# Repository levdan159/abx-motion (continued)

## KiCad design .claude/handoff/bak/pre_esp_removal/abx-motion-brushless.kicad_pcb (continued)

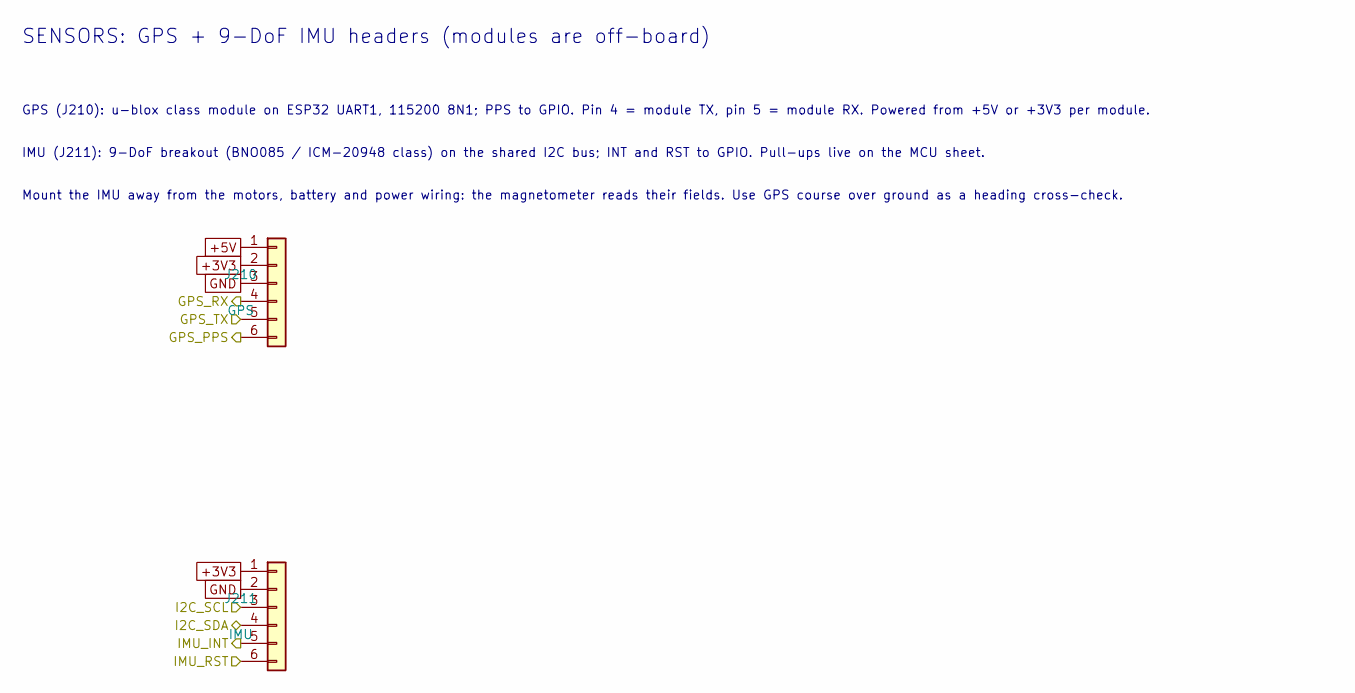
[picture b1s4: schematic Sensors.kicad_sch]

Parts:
J210: GPS; JST_PH_B6B-PH-K_1x06_P2.00mm_Vertical
J211: IMU; JST_PH_B6B-PH-K_1x06_P2.00mm_Vertical

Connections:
+3V3: J210.2, J211.1; also elsewhere on the board
+5V: J210.1; also elsewhere on the board
/GPS_PPS: J210.6; also elsewhere on the board
/GPS_RX: J210.4; also elsewhere on the board
/GPS_TX: J210.5; also elsewhere on the board
/I2C_SCL: J211.3; also elsewhere on the board
/I2C_SDA: J211.4; also elsewhere on the board
/IMU_INT: J211.5; also elsewhere on the board
/IMU_RST: J211.6; also elsewhere on the board

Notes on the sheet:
SENSORS: GPS + 9-DoF IMU headers (modules are off-board)
GPS (J210): u-blox class module on ESP32 UART1, 115200 8N1; PPS to GPIO. Pin 4 = module TX, pin 5 = module RX. Powered from +5V or +3V3 per module.
IMU (J211): 9-DoF breakout (BNO085 / ICM-20948 class) on the shared I2C bus; INT and RST to GPIO. Pull-ups live on the MCU sheet.
Mount the IMU away from the motors, battery and power wiring: the magnetometer reads their fields. Use GPS course over ground as a heading cross-check.

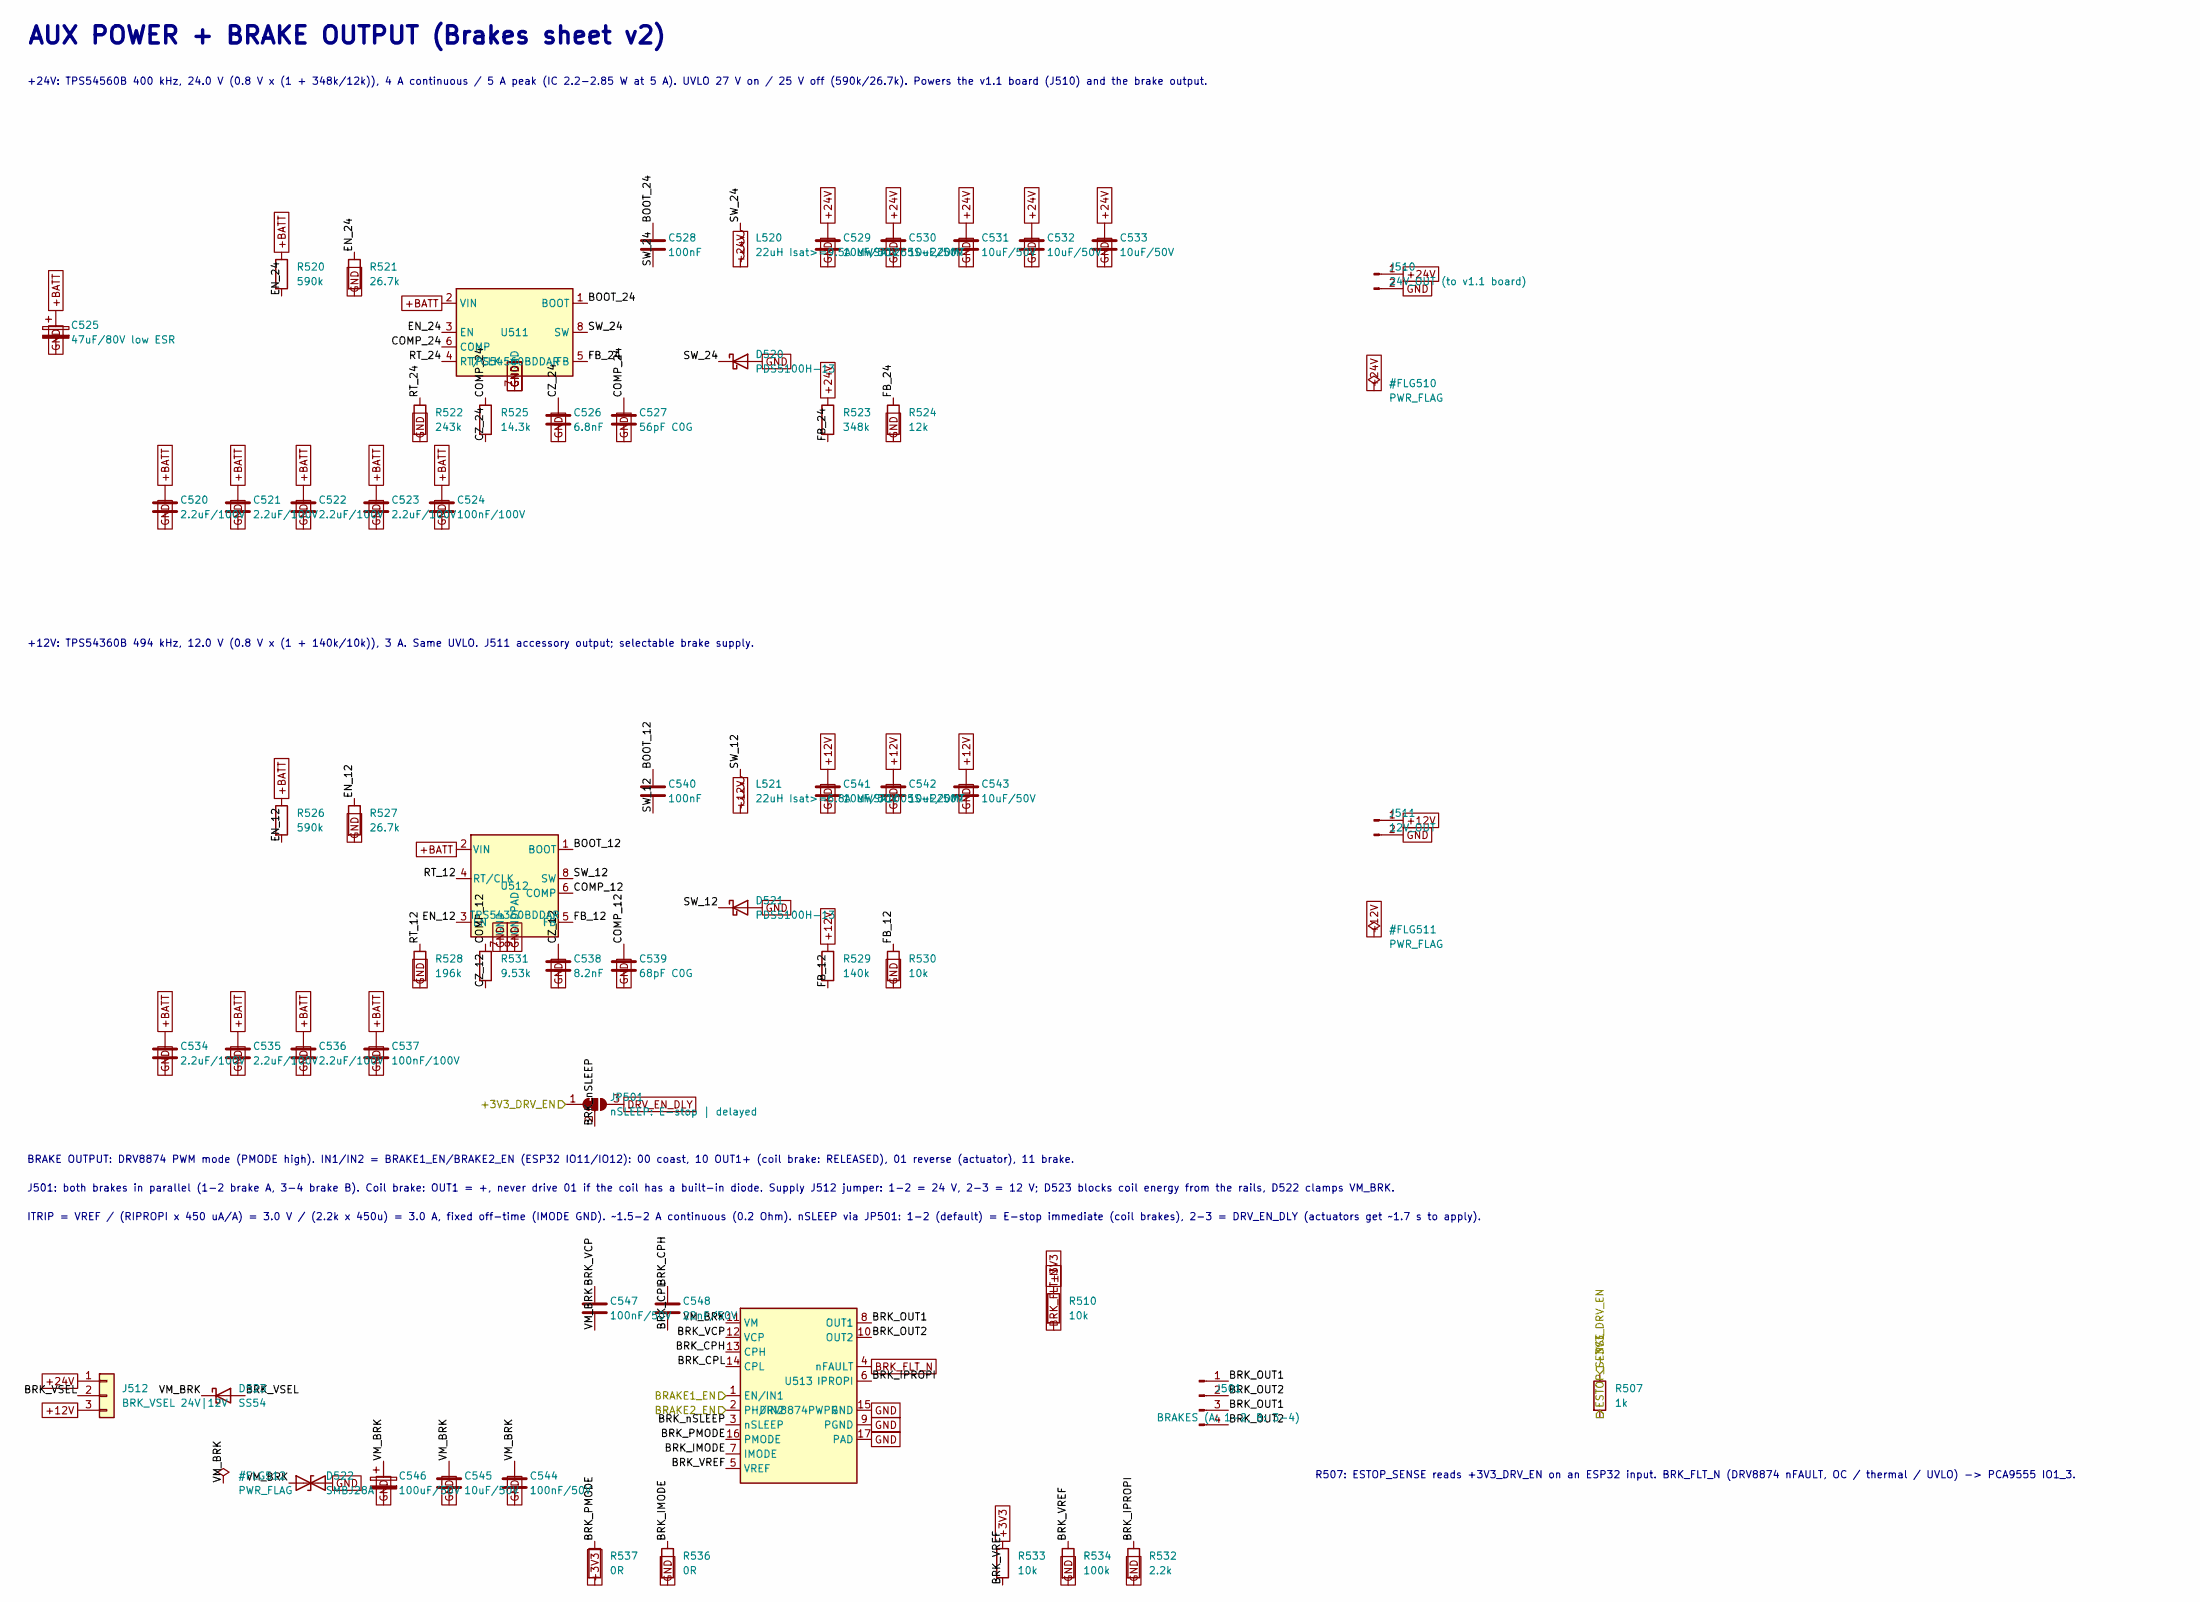
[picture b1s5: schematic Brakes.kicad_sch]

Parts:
C520, C521, C522, C523, C534, C535, C536: 2.2uF/100V; C_1210_3225Metric
C524, C537: 100nF/100V; C_0603_1608Metric
C525: 47uF/80V low ESR; CP_Elec_10x10.5
C526: 6.8nF; C_0603_1608Metric
C527: 56pF C0G; C_0603_1608Metric
C528, C540: 100nF; C_0603_1608Metric
C529, C530, C531, C532, C533, C541, C542, C543, C545: 10uF/50V; C_1210_3225Metric
C538: 8.2nF; C_0603_1608Metric
C539: 68pF C0G; C_0603_1608Metric
C544, C547: 100nF/50V; C_0603_1608Metric
C546: 100uF/50V; CP_Elec_8x10.5
C548: 22nF/50V; C_0603_1608Metric
D520, D521: PDS5100H-13; D_PowerDI-5
D522: SMBJ28A; D_SMB
D523: SS54; D_SMC
J501: BRAKES (A: 1-2, B: 3-4); TerminalBlock_Phoenix_MKDS-1,5-4-5.08_1x04_P5.08mm_Horizont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
J510: 24V_OUT (to v1.1 board); TerminalBlock_Phoenix_MKDS-1,5-2-5.08_1x02_P5.08mm_Horizont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
J511: 12V_OUT; TerminalBlock_Phoenix_MKDS-1,5-2-5.08_1x02_P5.08mm_Horizont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
J512: BRK_VSEL 24V|12V; PinHeader_1x03_P2.54mm_Vertical
JP501: nSLEEP: E-stop | delayed; SolderJumper-3_P1.3mm_Bridged12_RoundedPad1.0x1.5mm
L520: 22uH Isat>=9.5A MWSA1265S-220MT; L_Sunlord_MWSA1265S
L521: 22uH Isat>=6.8A MWSA1005S-220MT; L_Sunlord_MWSA1005S
R507: 1k; R_0603_1608Metric
R510, R530, R533: 10k; R_0603_1608Metric
R520, R526: 590k; R_0805_2012Metric
R521, R527: 26.7k; R_0603_1608Metric
R522: 243k; R_0603_1608Metric
R523: 348k; R_0603_1608Metric
R524: 12k; R_0603_1608Metric
R525: 14.3k; R_0603_1608Metric
R528: 196k; R_0603_1608Metric
R529: 140k; R_0603_1608Metric
R531: 9.53k; R_0603_1608Metric
R532: 2.2k; R_0603_1608Metric
R534: 100k; R_0603_1608Metric
R536, R537: 0R; R_0603_1608Metric
U511: TPS54560BDDAR; TI_SO-PowerPAD-8_ThermalVias
U512: TPS54360BDDAR; TI_SO-PowerPAD-8_ThermalVias
U513: DRV8874PWPR; HTSSOP-16-1EP_4.4x5mm_P0.65mm_EP3.4x5mm_Mask3x3mm_ThermalVi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

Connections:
+3V3: R510.1, R533.1, R537.2; also elsewhere on the board
+12V: C541.1, C542.1, C543.1, J511.1, J512.3, L521.2, R529.1
+24V: C529.1, C530.1, C531.1, C532.1, C533.1, J510.1, J512.1, L520.2, R523.1
+BATT: C520.1, C521.1, C522.1, C523.1, C524.1, C525.1, C534.1, C535.1, C536.1, C537.1, R520.1, R526.1, U511.2 (VIN), U512.2 (VIN); also elsewhere on the board
/+3V3_DRV_EN: JP501.1 (A), R507.1; also elsewhere on the board
/BRAKE1_EN: U513.1 (EN/IN1); also elsewhere on the board
/BRAKE2_EN: U513.2 (PH/IN2); also elsewhere on the board
/Brakes/BOOT_12: C540.1, U512.1 (BOOT)
/Brakes/BOOT_24: C528.1, U511.1 (BOOT)
/Brakes/BRK_CPH: C548.1, U513.13 (CPH)
/Brakes/BRK_CPL: C548.2, U513.14 (CPL)
/Brakes/BRK_IMODE: R536.1, U513.7 (IMODE)
/Brakes/BRK_IPROPI: R532.1, U513.6 (IPROPI)
/Brakes/BRK_OUT1: J501.1, J501.3, U513.8 (OUT1)
/Brakes/BRK_OUT2: J501.2, J501.4, U513.10 (OUT2)
/Brakes/BRK_PMODE: R537.1, U513.16 (PMODE)
/Brakes/BRK_VCP: C547.1, U513.12 (VCP)
/Brakes/BRK_VREF: R533.2, R534.1, U513.5 (VREF)
/Brakes/BRK_VSEL: D523.2 (A), J512.2
/Brakes/BRK_nSLEEP: JP501.2 (C), U513.3 (nSLEEP)
/Brakes/COMP_12: C539.1, R531.1, U512.6 (COMP)
/Brakes/COMP_24: C527.1, R525.1, U511.6 (COMP)
/Brakes/CZ_12: C538.1, R531.2
/Brakes/CZ_24: C526.1, R525.2
/Brakes/EN_12: R526.2, R527.1, U512.3 (EN)
/Brakes/EN_24: R520.2, R521.1, U511.3 (EN)
/Brakes/FB_12: R529.2, R530.1, U512.5 (FB)
/Brakes/FB_24: R523.2, R524.1, U511.5 (FB)
/Brakes/RT_12: R528.1, U512.4 (RT/CLK)
/Brakes/RT_24: R522.1, U511.4 (RT/CLK)
/Brakes/SW_12: C540.2, D521.1 (K), L521.1, U512.8 (SW)
/Brakes/SW_24: C528.2, D520.1 (K), L520.1, U511.8 (SW)
/Brakes/VM_BRK: C544.1, C545.1, C546.1, C547.2, D522.1 (A1), D523.1 (K), U513.11 (VM)
/ESTOP_SENSE: R507.2; also elsewhere on the board
BRK_FLT_N: R510.2, U513.4 (nFAULT); also elsewhere on the board
DRV_EN_DLY: JP501.3 (B); also elsewhere on the board

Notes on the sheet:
AUX POWER + BRAKE OUTPUT (Brakes sheet v2)
+24V: TPS54560B 400 kHz, 24.0 V (0.8 V x (1 + 348k/12k)), 4 A continuous / 5 A peak (IC 2.2-2.85 W at 5 A). UVLO 27 V on / 25 V off (590k/26.7k). Powers the v1.1 board (J510) and the brake output.
+12V: TPS54360B 494 kHz, 12.0 V (0.8 V x (1 + 140k/10k)), 3 A. Same UVLO. J511 accessory output; selectable brake supply.
BRAKE OUTPUT: DRV8874 PWM mode (PMODE high). IN1/IN2 = BRAKE1_EN/BRAKE2_EN (ESP32 IO11/IO12): 00 coast, 10 OUT1+ (coil brake: RELEASED), 01 reverse (actuator), 11 brake.
J501: both brakes in parallel (1-2 brake A, 3-4 brake B). Coil brake: OUT1 = +, never drive 01 if the coil has a built-in diode. Supply J512 jumper: 1-2 = 24 V, 2-3 = 12 V; D523 blocks coil energy from the rails, D522 clamps VM_BRK.
ITRIP = VREF / (RIPROPI x 450 uA/A) = 3.0 V / (2.2k x 450u) = 3.0 A, fixed off-time (IMODE GND). ~1.5-2 A continuous (0.2 Ohm). nSLEEP via JP501: 1-2 (default) = E-stop immediate (coil brakes), 2-3 = DRV_EN_DLY (actuators get ~1.7 s to apply).
R507: ESTOP_SENSE reads +3V3_DRV_EN on an ESP32 input. BRK_FLT_N (DRV8874 nFAULT, OC / thermal / UVLO) -> PCA9555 IO1_3.

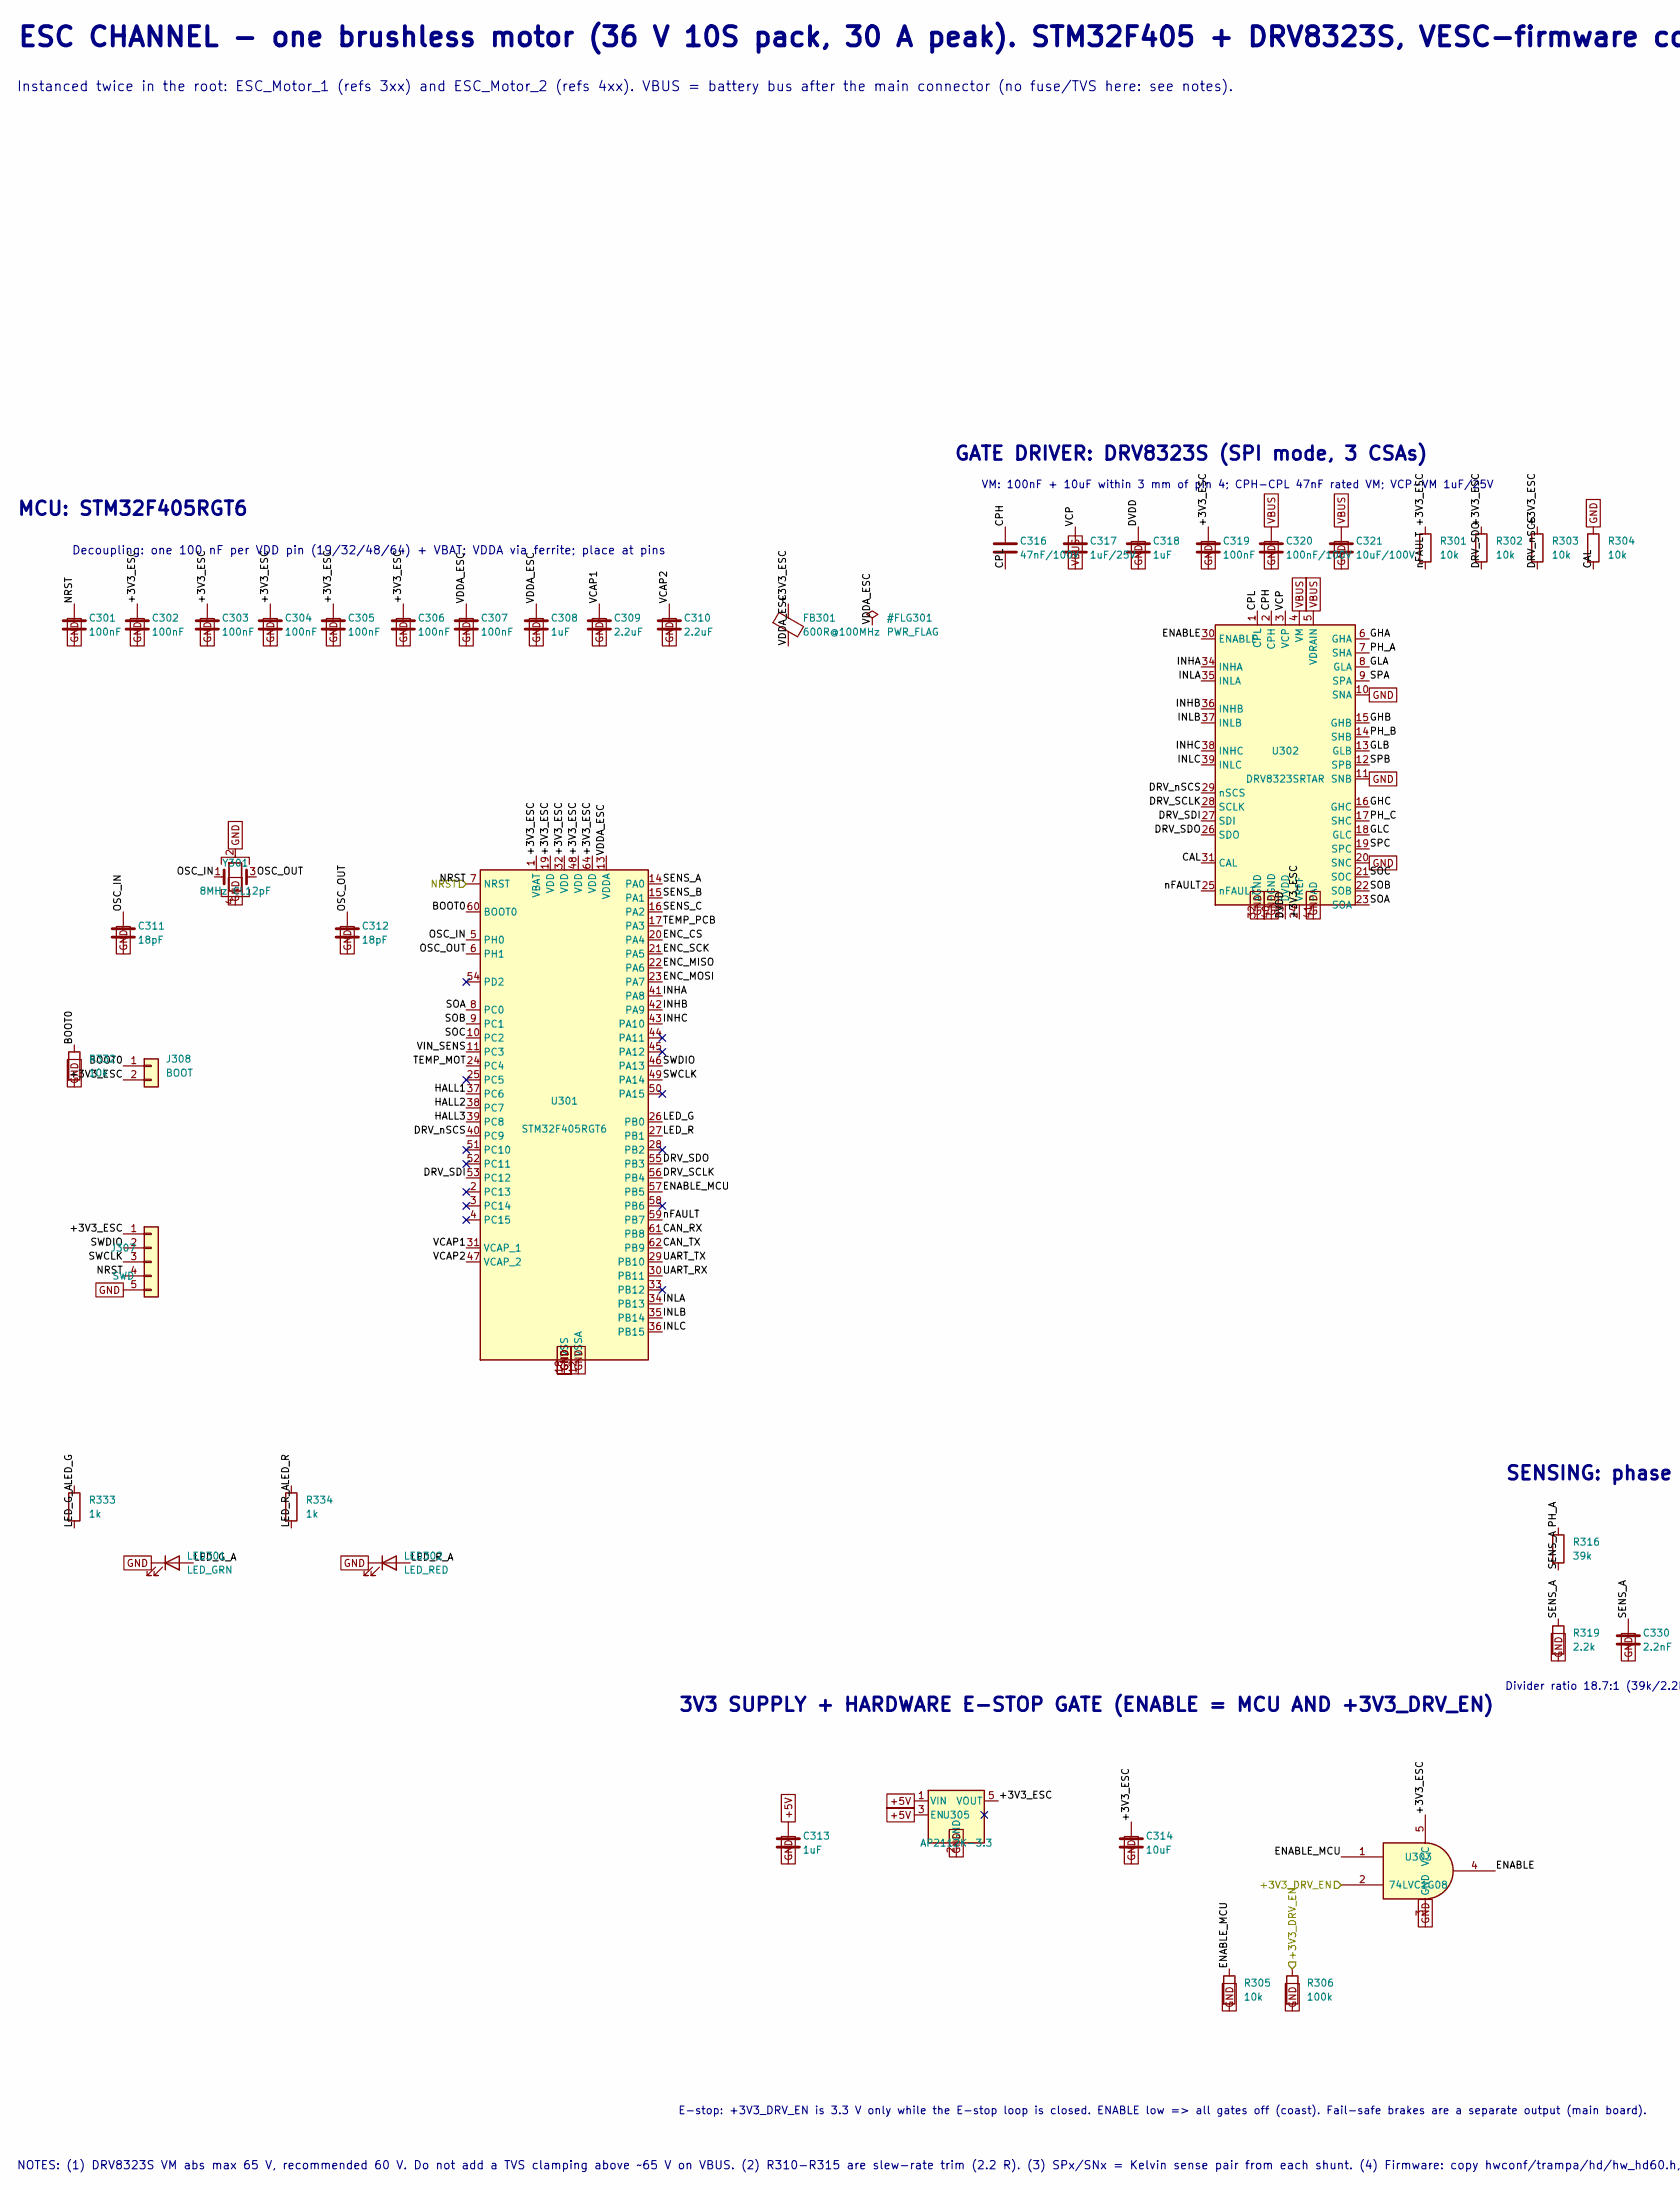
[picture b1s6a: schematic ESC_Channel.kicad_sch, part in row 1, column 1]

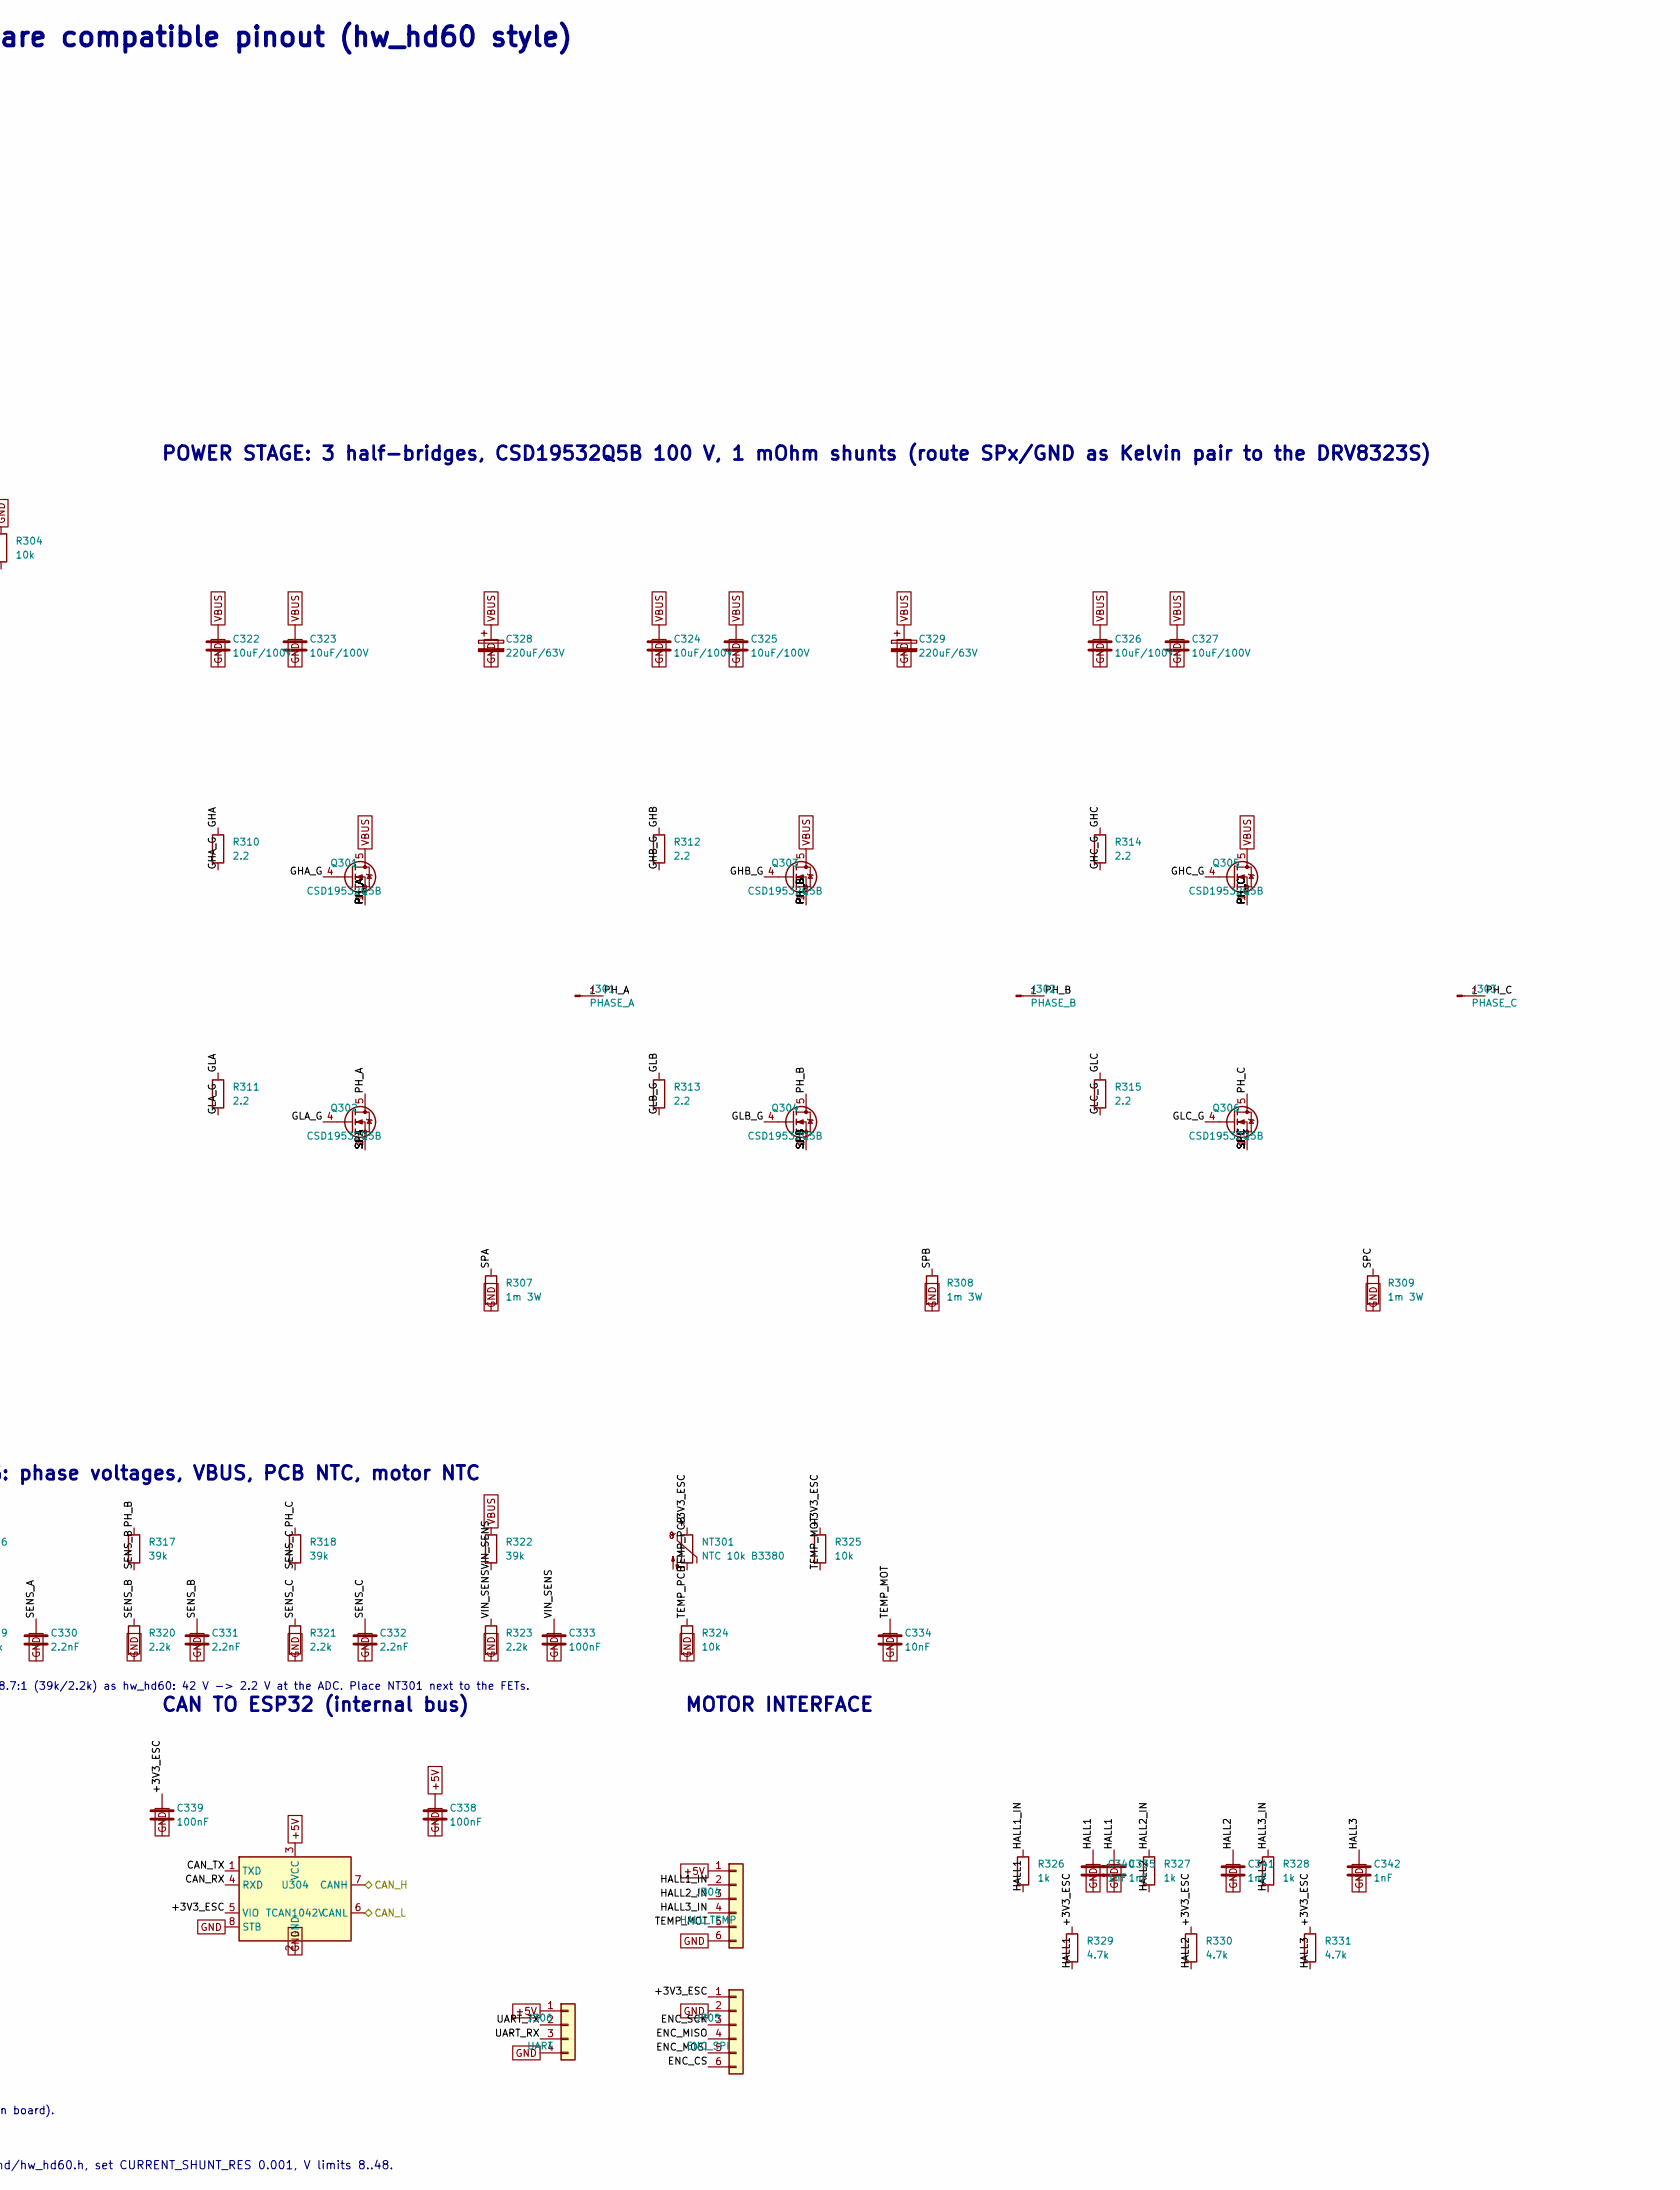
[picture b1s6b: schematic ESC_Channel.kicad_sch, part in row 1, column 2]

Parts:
C301, C302, C303, C304, C305, C306, C307, C319, C333, C338, C339: 100nF; C_0603_1608Metric
C308, C313, C318: 1uF; C_0603_1608Metric
C309, C310: 2.2uF; C_0603_1608Metric
C311, C312: 18pF; C_0603_1608Metric
C314: 10uF; C_0805_2012Metric
C316: 47nF/100V; C_0603_1608Metric
C317: 1uF/25V; C_0603_1608Metric
C320: 100nF/100V; C_0603_1608Metric
C321, C322, C323, C324, C325, C326, C327: 10uF/100V; C_1210_3225Metric
C328, C329: 220uF/63V; CP_Elec_10x10.5
C330, C331, C332: 2.2nF; C_0603_1608Metric
C334: 10nF; C_0603_1608Metric
C335, C340, C341, C342: 1nF; C_0603_1608Metric
FB301: 600R@100MHz; L_0603_1608Metric
J301: PHASE_A; SolderWirePad_1x01_SMD_5x10mm
J302: PHASE_B; SolderWirePad_1x01_SMD_5x10mm
J303: PHASE_C; SolderWirePad_1x01_SMD_5x10mm
J304: HALL_TEMP; JST_PH_B6B-PH-K_1x06_P2.00mm_Vertical
J305: ENC_SPI; JST_PH_B6B-PH-K_1x06_P2.00mm_Vertical
J306: UART; JST_PH_B4B-PH-K_1x04_P2.00mm_Vertical
J307: SWD; PinHeader_1x05_P2.54mm_Vertical
J308: BOOT; PinHeader_1x02_P2.54mm_Vertical
LED301: LED_GRN; LED_0603_1608Metric
LED302: LED_RED; LED_0603_1608Metric
NT301: NTC 10k B3380; R_0603_1608Metric
Q301, Q302, Q303, Q304, Q305, Q306: CSD19532Q5B; TDSON-8-1
R301, R302, R303, R304, R305, R324, R325, R332: 10k; R_0603_1608Metric
R306: 100k; R_0603_1608Metric
R307, R308, R309: 1m 3W; R_2512_6332Metric
R310, R311, R312, R313, R314, R315: 2.2; R_0603_1608Metric
R316, R317, R318, R322: 39k; R_0805_2012Metric
R319, R320, R321, R323: 2.2k; R_0603_1608Metric
R326, R327, R328, R333, R334: 1k; R_0603_1608Metric
R329, R330, R331: 4.7k; R_0603_1608Metric
U301: STM32F405RGT6; LQFP-64_10x10mm_P0.5mm
U302: DRV8323SRTAR; Texas_RTA0040B_WQFN-40-1EP_6x6mm_P0.5mm_EP4.15x4.15mm
U303: 74LVC1G08; SOT-23-5
U304: TCAN1042V; SOIC-8_3.9x4.9mm_P1.27mm
U305: AP2112K-3.3; SOT-23-5
Y301: 8MHz CL12pF; Crystal_SMD_3225-4Pin_3.2x2.5mm

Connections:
+5V: C313.1, C338.1, J304.1, J306.1, U304.3 (VCC), U305.1 (VIN), U305.3 (EN); also elsewhere on the board
/DRV_SCLK: U301.56 (PB4), U302.28 (SCLK); also elsewhere on the board
/DRV_SDI: U301.53 (PC12), U302.27 (SDI); also elsewhere on the board
/DRV_SDO: R302.2, U301.55 (PB3), U302.26 (SDO); also elsewhere on the board
/ESC_Motor_1/CAL: R304.2, U302.31 (CAL)
/ESC_Motor_1/CPH: C316.1, U302.2 (CPH)
/ESC_Motor_1/CPL: C316.2, U302.1 (CPL)
/ESC_Motor_1/DVDD: C318.1, U302.33 (DVDD)
/ESC_Motor_1/GHA: R310.1, U302.6 (GHA)
/ESC_Motor_1/GHA_G: Q301.4 (G), R310.2
/ESC_Motor_1/GHB: R312.1, U302.15 (GHB)
/ESC_Motor_1/GHB_G: Q303.4 (G), R312.2
/ESC_Motor_1/GHC: R314.1, U302.16 (GHC)
/ESC_Motor_1/GHC_G: Q305.4 (G), R314.2
/ESC_Motor_1/GLA: R311.1, U302.8 (GLA)
/ESC_Motor_1/GLA_G: Q302.4 (G), R311.2
/ESC_Motor_1/GLB: R313.1, U302.13 (GLB)
/ESC_Motor_1/GLB_G: Q304.4 (G), R313.2
/ESC_Motor_1/GLC: R315.1, U302.18 (GLC)
/ESC_Motor_1/GLC_G: Q306.4 (G), R315.2
/ESC_Motor_1/HALL1_IN: J304.2, R326.1
/ESC_Motor_1/HALL2_IN: J304.3, R327.1
/ESC_Motor_1/HALL3_IN: J304.4, R328.1
/ESC_Motor_1/PH_A: J301.1, Q301.1 (S), Q301.2 (S), Q301.3 (S), Q302.5 (D), R316.1, U302.7 (SHA)
/ESC_Motor_1/PH_B: J301.2, Q303.1 (S), Q303.2 (S), Q303.3 (S), Q304.5 (D), R317.1, U302.14 (SHB)
/ESC_Motor_1/PH_C: J301.3, Q305.1 (S), Q305.2 (S), Q305.3 (S), Q306.5 (D), R318.1, U302.17 (SHC)
/ESC_Motor_1/SPA: Q302.1 (S), Q302.2 (S), Q302.3 (S), R307.1, U302.9 (SPA)
/ESC_Motor_1/SPB: Q304.1 (S), Q304.2 (S), Q304.3 (S), R308.1, U302.12 (SPB)
/ESC_Motor_1/SPC: Q306.1 (S), Q306.2 (S), Q306.3 (S), R309.1, U302.19 (SPC)
/ESC_Motor_1/VCP: C317.1, U302.3 (VCP)
/M1_ENABLE: U302.30 (ENABLE); also elsewhere on the board
/M1_HALL1: C340.1, R326.2, R329.2; also elsewhere on the board
/M1_HALL2: C341.1, R327.2, R330.2; also elsewhere on the board
/M1_HALL3: C342.1, R328.2, R331.2; also elsewhere on the board
/M1_INHA: U302.34 (INHA); also elsewhere on the board
/M1_INHB: U302.36 (INHB); also elsewhere on the board
/M1_INHC: U302.38 (INHC); also elsewhere on the board
/M1_INLA: U302.35 (INLA); also elsewhere on the board
/M1_INLB: U302.37 (INLB); also elsewhere on the board
/M1_INLC: U302.39 (INLC); also elsewhere on the board
/M1_SENS_A: C330.1, R316.2, R319.1; also elsewhere on the board
/M1_SENS_B: C331.1, R317.2, R320.1; also elsewhere on the board
/M1_SENS_C: C332.1, R318.2, R321.1; also elsewhere on the board
/M1_SOA: U302.23 (SOA); also elsewhere on the board
/M1_SOB: U302.22 (SOB); also elsewhere on the board
/M1_SOC: U302.21 (SOC); also elsewhere on the board
/M1_TEMP_MOT: C334.1, J304.5, R325.2; also elsewhere on the board
/M1_nFAULT: R301.2, U302.25 (nFAULT); also elsewhere on the board
/M1_nSCS: R303.2, U302.29 (nSCS); also elsewhere on the board
unnamed: C301.1, J307.4, U301.7 (NRST)
unnamed: C307.1, C308.1, FB301.2, U301.13 (VDDA)
unnamed: C309.1, U301.31 (VCAP_1)
unnamed: C310.1, U301.47 (VCAP_2)
unnamed: C311.1, U301.5 (PH0), Y301.1
unnamed: C312.1, U301.6 (PH1), Y301.3
unnamed: C333.1, R322.2, R323.1, U301.11 (PC3)
unnamed: J305.3, U301.21 (PA5)
unnamed: J305.4, U301.22 (PA6)
unnamed: J305.5, U301.23 (PA7)
unnamed: J305.6, U301.20 (PA4)
unnamed: J306.2, U301.29 (PB10)
unnamed: J306.3, U301.30 (PB11)
unnamed: J307.2, U301.46 (PA13)
unnamed: J307.3, U301.49 (PA14)
unnamed: J308.1, R332.1, U301.60 (BOOT0)
unnamed: LED301.2 (A), R333.2
unnamed: LED302.2 (A), R334.2
unnamed: R305.1, U301.57 (PB5), U303.1
unnamed: R306.1, U303.2
unnamed: R333.1, U301.26 (PB0)
unnamed: R334.1, U301.27 (PB1)
unnamed: U301.61 (PB8), U304.4 (RXD)
unnamed: U301.62 (PB9), U304.1 (TXD)
VBUS: C317.2, C320.1, C321.1, C322.1, C323.1, C324.1, C325.1, C326.1, C327.1, C328.1, C329.1, Q301.5 (D), Q303.5 (D), Q305.5 (D), R322.1, U302.4 (VM), U302.5 (VDRAIN); also elsewhere on the board

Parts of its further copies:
C416: 47nF/100V; C_0603_1608Metric
C417: 1uF/25V; C_0603_1608Metric
C418: 1uF; C_0603_1608Metric
C419: 100nF; C_0603_1608Metric
C420: 100nF/100V; C_0603_1608Metric
C421, C422, C423, C424, C425, C426, C427: 10uF/100V; C_1210_3225Metric
C428, C429: 220uF/63V; CP_Elec_10x10.5
C430, C431, C432: 2.2nF; C_0603_1608Metric
C434: 10nF; C_0603_1608Metric
C440, C441, C442: 1nF; C_0603_1608Metric
J404: HALL_TEMP; JST_PH_B6B-PH-K_1x06_P2.00mm_Vertical
Q401, Q402, Q403, Q404, Q405, Q406: CSD19532Q5B; TDSON-8-1
R401, R402, R403, R404, R424, R425: 10k; R_0603_1608Metric
R407, R408, R409: 1m 3W; R_2512_6332Metric
R410, R411, R412, R413, R414, R415: 2.2; R_0603_1608Metric
R416, R417, R418: 39k; R_0805_2012Metric
R419, R420, R421: 2.2k; R_0603_1608Metric
R426, R427, R428: 1k; R_0603_1608Metric
R429, R430, R431: 4.7k; R_0603_1608Metric
U402: DRV8323SRTAR; Texas_RTA0040B_WQFN-40-1EP_6x6mm_P0.5mm_EP4.15x4.15mm

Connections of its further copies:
+5V: J404.1; also elsewhere on the board
/DRV_SCLK: U402.28 (SCLK); also elsewhere on the board
/DRV_SDI: U402.27 (SDI); also elsewhere on the board
/DRV_SDO: R402.2, U402.26 (SDO); also elsewhere on the board
/ESC_Motor_2/CAL: R404.2, U402.31 (CAL)
/ESC_Motor_2/CPH: C416.1, U402.2 (CPH)
/ESC_Motor_2/CPL: C416.2, U402.1 (CPL)
/ESC_Motor_2/DVDD: C418.1, U402.33 (DVDD)
/ESC_Motor_2/GHA: R410.1, U402.6 (GHA)
/ESC_Motor_2/GHA_G: Q401.4 (G), R410.2
/ESC_Motor_2/GHB: R412.1, U402.15 (GHB)
/ESC_Motor_2/GHB_G: Q403.4 (G), R412.2
/ESC_Motor_2/GHC: R414.1, U402.16 (GHC)
/ESC_Motor_2/GHC_G: Q405.4 (G), R414.2
/ESC_Motor_2/GLA: R411.1, U402.8 (GLA)
/ESC_Motor_2/GLA_G: Q402.4 (G), R411.2
/ESC_Motor_2/GLB: R413.1, U402.13 (GLB)
/ESC_Motor_2/GLB_G: Q404.4 (G), R413.2
/ESC_Motor_2/GLC: R415.1, U402.18 (GLC)
/ESC_Motor_2/GLC_G: Q406.4 (G), R415.2
/ESC_Motor_2/HALL1_IN: J404.2, R426.1
/ESC_Motor_2/HALL2_IN: J404.3, R427.1
/ESC_Motor_2/HALL3_IN: J404.4, R428.1
/ESC_Motor_2/PH_A: Q401.1 (S), Q401.2 (S), Q401.3 (S), Q402.5 (D), R416.1, U402.7 (SHA); also elsewhere on the board
/ESC_Motor_2/PH_B: Q403.1 (S), Q403.2 (S), Q403.3 (S), Q404.5 (D), R417.1, U402.14 (SHB); also elsewhere on the board
/ESC_Motor_2/PH_C: Q405.1 (S), Q405.2 (S), Q405.3 (S), Q406.5 (D), R418.1, U402.17 (SHC); also elsewhere on the board
/ESC_Motor_2/SPA: Q402.1 (S), Q402.2 (S), Q402.3 (S), R407.1, U402.9 (SPA)
/ESC_Motor_2/SPB: Q404.1 (S), Q404.2 (S), Q404.3 (S), R408.1, U402.12 (SPB)
/ESC_Motor_2/SPC: Q406.1 (S), Q406.2 (S), Q406.3 (S), R409.1, U402.19 (SPC)
/ESC_Motor_2/VCP: C417.1, U402.3 (VCP)
/M2_ENABLE: U402.30 (ENABLE); also elsewhere on the board
/M2_HALL1: C440.1, R426.2, R429.2; also elsewhere on the board
/M2_HALL2: C441.1, R427.2, R430.2; also elsewhere on the board
/M2_HALL3: C442.1, R428.2, R431.2; also elsewhere on the board
/M2_INHA: U402.34 (INHA); also elsewhere on the board
/M2_INHB: U402.36 (INHB); also elsewhere on the board
/M2_INHC: U402.38 (INHC); also elsewhere on the board
/M2_INLA: U402.35 (INLA); also elsewhere on the board
/M2_INLB: U402.37 (INLB); also elsewhere on the board
/M2_INLC: U402.39 (INLC); also elsewhere on the board
/M2_SENS_A: C430.1, R416.2, R419.1; also elsewhere on the board
/M2_SENS_B: C431.1, R417.2, R420.1; also elsewhere on the board
/M2_SENS_C: C432.1, R418.2, R421.1; also elsewhere on the board
/M2_SOA: U402.23 (SOA); also elsewhere on the board
/M2_SOB: U402.22 (SOB); also elsewhere on the board
/M2_SOC: U402.21 (SOC); also elsewhere on the board
/M2_TEMP_MOS: R424.2; also elsewhere on the board
/M2_TEMP_MOT: C434.1, J404.5, R425.2; also elsewhere on the board
/M2_nFAULT: R401.2, U402.25 (nFAULT); also elsewhere on the board
/M2_nSCS: R403.2, U402.29 (nSCS); also elsewhere on the board
VBUS: C417.2, C420.1, C421.1, C422.1, C423.1, C424.1, C425.1, C426.1, C427.1, C428.1, C429.1, Q401.5 (D), Q403.5 (D), Q405.5 (D), U402.4 (VM), U402.5 (VDRAIN); also elsewhere on the board

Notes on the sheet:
ESC CHANNEL - one brushless motor (36 V 10S pack, 30 A peak). STM32F405 + DRV8323S, VESC-firmware compatible pinout (hw_hd60 style)
Instanced twice in the root: ESC_Motor_1 (refs 3xx) and ESC_Motor_2 (refs 4xx). VBUS = battery bus after the main connector (no fuse/TVS here: see notes).
MCU: STM32F405RGT6
GATE DRIVER: DRV8323S (SPI mode, 3 CSAs)
POWER STAGE: 3 half-bridges, CSD19532Q5B 100 V, 1 mOhm shunts (route SPx/GND as Kelvin pair to the DRV8323S)
SENSING: phase voltages, VBUS, PCB NTC, motor NTC
3V3 SUPPLY + HARDWARE E-STOP GATE (ENABLE = MCU AND +3V3_DRV_EN)
CAN TO ESP32 (internal bus)
MOTOR INTERFACE
NOTES: (1) DRV8323S VM abs max 65 V, recommended 60 V. Do not add a TVS clamping above ~65 V on VBUS. (2) R310-R315 are slew-rate trim (2.2 R). (3) SPx/SNx = Kelvin sense pair from each shunt. (4) Firmware: copy hwconf/trampa/hd/hw_hd60.h, set CURRENT_SHUNT_RES 0.001, V limits 8..48.
Decoupling: one 100 nF per VDD pin (19/32/48/64) + VBAT; VDDA via ferrite; place at pins
VM: 100nF + 10uF within 3 mm of pin 4; CPH-CPL 47nF rated VM; VCP-VM 1uF/25V
Divider ratio 18.7:1 (39k/2.2k) as hw_hd60: 42 V -> 2.2 V at the ADC. Place NT301 next to the FETs.
E-stop: +3V3_DRV_EN is 3.3 V only while the E-stop loop is closed. ENABLE low => all gates off (coast). Fail-safe brakes are a separate output (main board).
